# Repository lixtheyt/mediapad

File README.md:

<div align="center">

# MediaPad

**A 9 key hackpad with a rotary encoder, an OLED display and 20 LEDs that controls whatever is playing on your computer, and shows it to you on its own screen.**

<!-- HELYX_STATUS_START -->
<!-- HELYX_STATUS_END -->

</div>

## Table of contents

- [Features](#features)
- [Video](#video)
- [Quick start](#quick-start)
- [Build it yourself](#build-it-yourself)
    - [BOM](#bom)
    - [Case](#case)
    - [PCB](#pcb)
    - [IRL results](#irl-results)
- [Firmware](#firmware)
    - [Two builds](#two-builds)
    - [The keys](#the-keys)
    - [Rotary encoder](#rotary-encoder)
    - [RGB](#rgb)
    - [Help browser](#help-browser)
    - [OLED](#oled)
    - [Hidden key combos](#hidden-key-combos)
- [Companion app](#companion-app)
- [Credits](#credits)
- [License](#license)

## Features

- **128x32 OLED display**, with the title, artist and progress of whatever is playing.
- **EC11 rotary encoder**, which does something different in each of its six modes.
- **20 SK6812 MINI-E LEDs**. We gotta make somethin' for party nah??
- **Eight media keys**, the same on every mode except RGB, where they mix the colours.
- **A cool designed case**, printed in 8 pieces.

## Video

Click the picture to watch it.

## Quick start

Everything you need to make one is in [`Production`](Production):

| File | What it is |
| --- | --- |
| `gerbers.zip` | the PCB, ready to send to a manufacturer |
| `topCase.stl`, `middleCase.stl`, `bottomCase.stl` | the three parts of the case |
| `spacer.stl` | the spacer for the glow, print 6 |
| `support_display.stl` | the support for the OLED display |
| `mediapad_rev20_lixtheyt.uf2` | firmware for a board with all 20 LEDs |
| `mediapad_rev16_lixtheyt.uf2` | firmware for a board with 16 LEDs |

To flash it, hold the top left key while plugging the board in. It shows up as a drive on your
computer. Copy the `.uf2` that matches your board onto it and it restarts by itself.

Then start [`Companion/mediapad_tray.exe`](Companion), so the display knows what is playing.

## Build it yourself

### BOM

- 8x Cherry MX Switches
- 8x Keycaps
- 6x M3x5x4 Heatset inserts
- 6x M3x16mm Screws
- 8x 1N4148 DO-35 Diodes
- 16x/20x SK6812 MINI-E LEDs (16x = encoder has no LEDs)
- 1x 0.91" 128x32 OLED Display
- 1x EC11 Rotary Encoder
- 1x XIAO RP2040
- 1x Case (1x bottom case, 1x middle case, 1x top case)
- 6x Spacers (printed part)
- 1x Display Support (printed part, use a double-sided tape so it will hold)

### Case

Everything fits together using 6 M3 Bolts and heatset inserts. 4 for the case and 2 for the PCB.

It has 8 separate printed pieces.
3 are parts of the case, 1 is a spacer for the glow and 1 is for the OLED display as a support.

### PCB

I made my PCB inside KiCad.
Libraries I used were originally from the Hackpad website but I also used some that I had found on [grabcad](https://grabcad.com/library).

**Schematic**

**Board**

### IRL results

<div align="center">

</div>

## Firmware

This hackpad uses [QMK](https://qmk.fm/) firmware for everything.

### Two builds

The board exists in two LED populations, so the firmware ships as two revisions.
They differ only in the LED map keys, encoder and OLED are shared.

| Revision | LEDs | Board |
| --- | --- | --- |
| `rev20` | D1-D20 | fully populated |
| `rev16` | D1-D16 | built without the four LEDs ringing the encoder |

The four LEDs `rev16` leaves out are last in the WS2812 chain, so the remaining
sixteen still light normally. The idle screen prints the count
(`mediapad 16 LED`) so you can tell which build is on the board.

```bash
make mediapad/rev20:lixtheyt
```

### The keys

All eight switches are media keys, on every mode except RGB. Only what the
encoder does changes from mode to mode.

```
SW1 play/pause   SW2 rewind       SW3 fast forward   SW6 mute
SW4 prev track   SW5 next track
SW7 repeat       SW8 shuffle      SW9 = the encoder
```

### Rotary encoder

Clicking the encoder opens a mode picker that **previews** rather than switches:

* **Click** - opens it, showing the mode you are already in
* **Turn** - walks the list, nothing has changed yet
* **Click again** - confirms, and only now does the mode change
* **Wait** - it lapses and you stay exactly where you were

1. **Volume** - volume up / down
2. **Track skip** - next / previous track
3. **Arrows** - arrow up / down
4. **Scroll** - mouse wheel up / down
5. **Zoom** - zoom in / out, sent as Ctrl + wheel so it does not depend on your
   keyboard layout
6. **RGB** - the lighting, below

### RGB

RGB contains 16 effects. The first six run their own colours
(Pinwheel, Vortex, Rainbow wave, Chevron, Splash, Raindrops), the other ten come
out in whatever you mix, and several of those react to keypresses and spread
outward from the key you hit.

The keys aim the dial, and the dial does the changing:

```
SW1 red   SW2 green   SW3 blue   SW6 brightness   SW4 effect list
```

Whatever you set is remembered. The colour, the brightness and the effect are saved a few seconds
after you stop turning the dial, so they are still there after you unplug the board.

### Help browser

Press **play/pause + rewind together** if you forget what a key does. Turn the
encoder to walk the list, click it for the answer, press anything to back out.
The list follows whichever mode you opened it from.

The LEDs either side of that key light up
with the key itself as the dark gap between them, and the display spells the
position out in words. The words are the part that always works. The LED grid
sits about half a key pitch off the switch grid, so no single LED can point at a
key without also looking like it points at its neighbour.

### OLED

While something is playing, a scrolling title and artist, a progress bar, and a
bottom row carrying play/pause on the left, the clock, and shuffle / repeat
symbols on the right. The clock runs locally rather than echoing the host,
because Windows only refreshes its playback position every few seconds.

Otherwise: the board name and LED count, the current mode, and either
`waiting for app` (nothing arriving) or `nothing playing` (the app is connected,
but Windows has no media session).

The display turns itself off after five minutes with no key pressed, no turn of the encoder and
nothing playing, so the idle screen does not burn into the OLED. Any key, any turn or a track that
starts playing turns it back on.

### Hidden key combos

Armed on the media modes only. On the RGB mode those same switches are colour
controls.

| Hold | For | Does |
| --- | --- | --- |
| rewind + fast forward + mute | 5 s | bootloader |
| repeat + shuffle + mute | 5 s | clear EEPROM |
| rewind + fast forward | 2 s | reboot |
| repeat + shuffle | 2 s | toggle debug |

You can also reach the bootloader by holding the top left key while plugging in,
or by double-tapping the reset button on the XIAO.

## Companion app

`Companion/mediapad_tray.exe` is a portable application made in Python that feeds MediaPad with the latest
information about current played media on your computer. Without it the OLED shows the board name and
`waiting for app`, everything except the now-playing screen still works.

As I have mentioned... it is a portable application. That means you don't have to install anything.
Just open, mess with it in the tray (where background applications are located) and make sure to enable
the setting that allows it to open on start up of your computer, so you don't have to turn it on manually
every time you turn on your computer. If you've got no idea where the tray with the background applications
is located then please, [google it](https://www.google.com/search?q=Where+is+the+background+tray+located?).

## Credits

- [QMK](https://qmk.fm/), the firmware everything here runs on.
- [KiCad](https://www.kicad.org/) for the PCB and [Blender](https://www.blender.org/) for the case.
- The [Hackpad](https://hackpad.hackclub.com/) guide by Hack Club, where the first libraries came from.

I want to note out that the firmware was mostly done by AI due to my limited C knowledge
and the difficulty to create a firmware that does such advanced things.

## License

[MIT](LICENSE)

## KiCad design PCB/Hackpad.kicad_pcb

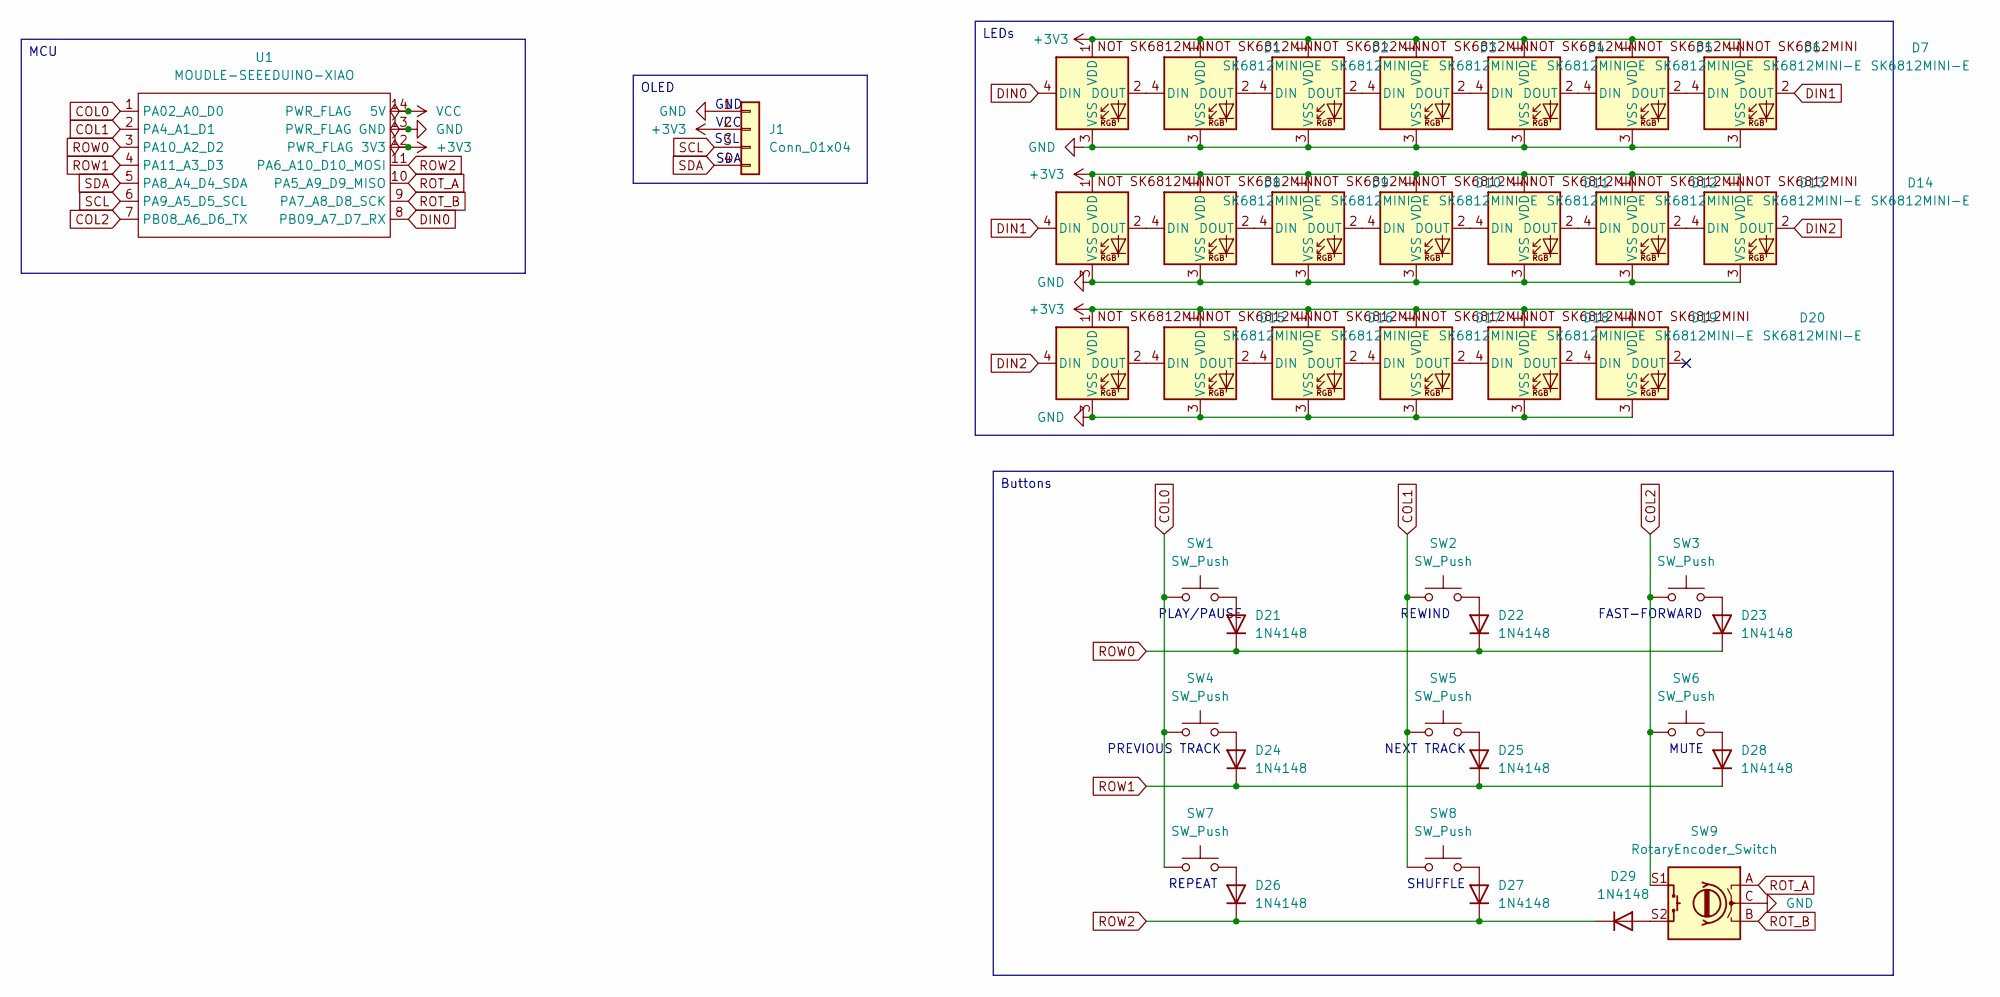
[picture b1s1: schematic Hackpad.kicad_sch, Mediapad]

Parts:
D1, D2, D3, D4, D5, D6, D7, D8, D9, D10, D11, D12, D13, D14, D15, D16, D17, D18, D19, D20: SK6812MINI-E; SK6812MINI-E_fixed
D21, D22, D23, D24, D25, D26, D27, D28, D29: 1N4148; D_DO-35_SOD27_P7.62mm_Horizontal
J1: Conn_01x04; SSD1306-0.91-OLED-4pin-128x32
SW1, SW2, SW3, SW4, SW5, SW6, SW7, SW8: SW_Push; SW_Cherry_MX_1.00u_PCB
SW9: RotaryEncoder_Switch; RotaryEncoder_Alps_EC11E-Switch_Vertical_H20mm
U1: MOUDLE-SEEEDUINO-XIAO; XIAO-Generic-Hybrid-14P-2.54-21X17.8MM

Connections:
+3V3: D1.1 (VDD), D2.1 (VDD), D3.1 (VDD), D4.1 (VDD), D5.1 (VDD), D6.1 (VDD), D7.1 (VDD), D8.1 (VDD), D9.1 (VDD), D10.1 (VDD), D11.1 (VDD), D12.1 (VDD), D13.1 (VDD), D14.1 (VDD), D15.1 (VDD), D16.1 (VDD), D17.1 (VDD), D18.1 (VDD), D19.1 (VDD), D20.1 (VDD), J1.2, U1.12 (3V3)
COL0: SW1.1, SW4.1, SW7.1, U1.1 (PA02_A0_D0)
COL1: SW2.1, SW5.1, SW8.1, U1.2 (PA4_A1_D1)
COL2: SW3.1, SW6.1, SW9.S1, U1.7 (PB08_A6_D6_TX)
DIN0: D1.4 (DIN), U1.8 (PB09_A7_D7_RX)
DIN1: D7.2 (DOUT), D8.4 (DIN)
DIN2: D14.2 (DOUT), D15.4 (DIN)
GND: D1.3 (VSS), D2.3 (VSS), D3.3 (VSS), D4.3 (VSS), D5.3 (VSS), D6.3 (VSS), D7.3 (VSS), D8.3 (VSS), D9.3 (VSS), D10.3 (VSS), D11.3 (VSS), D12.3 (VSS), D13.3 (VSS), D14.3 (VSS), D15.3 (VSS), D16.3 (VSS), D17.3 (VSS), D18.3 (VSS), D19.3 (VSS), D20.3 (VSS), J1.1, SW9.C, U1.13 (GND)
unnamed: D1.2 (DOUT), D2.4 (DIN)
unnamed: D2.2 (DOUT), D3.4 (DIN)
unnamed: D3.2 (DOUT), D4.4 (DIN)
unnamed: D4.2 (DOUT), D5.4 (DIN)
unnamed: D5.2 (DOUT), D6.4 (DIN)
unnamed: D6.2 (DOUT), D7.4 (DIN)
unnamed: D8.2 (DOUT), D9.4 (DIN)
unnamed: D9.2 (DOUT), D10.4 (DIN)
unnamed: D10.2 (DOUT), D11.4 (DIN)
unnamed: D11.2 (DOUT), D12.4 (DIN)
unnamed: D12.2 (DOUT), D13.4 (DIN)
unnamed: D13.2 (DOUT), D14.4 (DIN)
unnamed: D15.2 (DOUT), D16.4 (DIN)
unnamed: D16.2 (DOUT), D17.4 (DIN)
unnamed: D17.2 (DOUT), D18.4 (DIN)
unnamed: D18.2 (DOUT), D19.4 (DIN)
unnamed: D19.2 (DOUT), D20.4 (DIN)
unnamed: D21.2 (A), SW1.2
unnamed: D22.2 (A), SW2.2
unnamed: D23.2 (A), SW3.2
unnamed: D24.2 (A), SW4.2
unnamed: D25.2 (A), SW5.2
unnamed: D26.2 (A), SW7.2
unnamed: D27.2 (A), SW8.2
unnamed: D28.2 (A), SW6.2
unnamed: D29.2 (A), SW9.S2
ROT_A: SW9.A, U1.10 (PA5_A9_D9_MISO)
ROT_B: SW9.B, U1.9 (PA7_A8_D8_SCK)
ROW0: D21.1 (K), D22.1 (K), D23.1 (K), U1.3 (PA10_A2_D2)
ROW1: D24.1 (K), D25.1 (K), D28.1 (K), U1.4 (PA11_A3_D3)
ROW2: D26.1 (K), D27.1 (K), D29.1 (K), U1.11 (PA6_A10_D10_MOSI)
SCL: J1.3, U1.6 (PA9_A5_D5_SCL)
SDA: J1.4, U1.5 (PA8_A4_D4_SDA)
VCC: U1.14 (5V)

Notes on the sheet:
SDA
REWIND
PREVIOUS TRACK
REPEAT
VCC
SHUFFLE
GND
PLAY/PAUSE
SCL
MUTE
FAST-FORWARD
NEXT TRACK
OLED
LEDs
Buttons
MCU

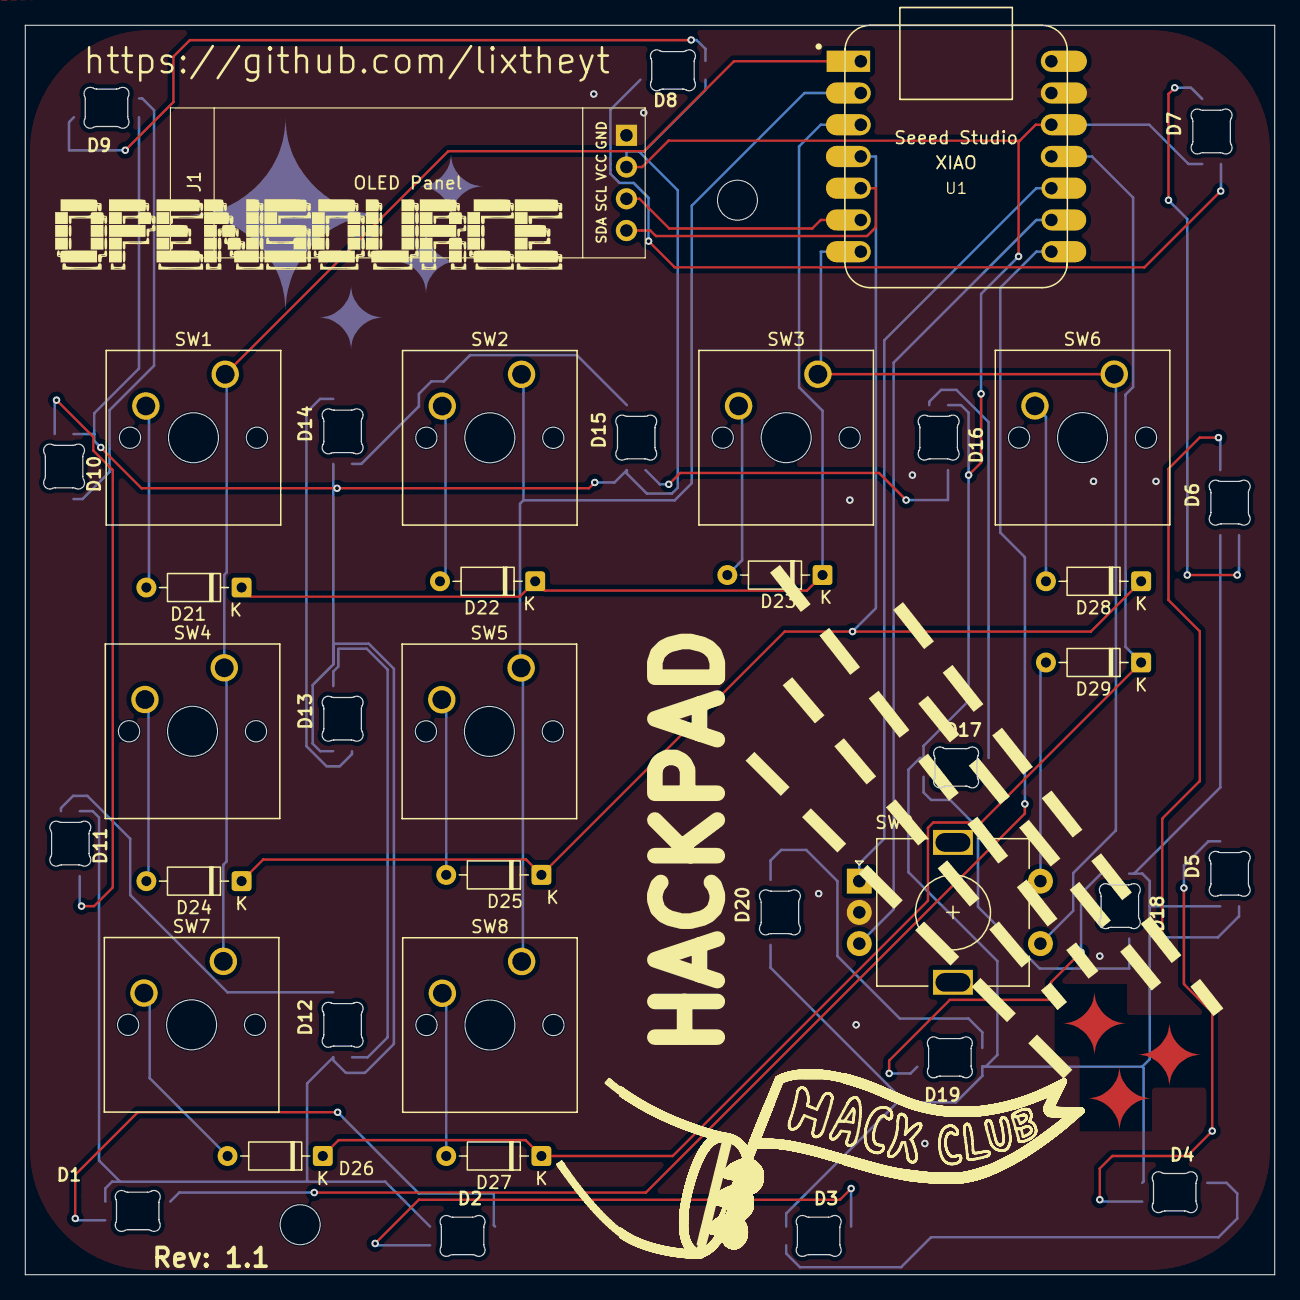
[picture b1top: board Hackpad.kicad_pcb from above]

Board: 2 copper layers, 100.0 x 100.0 mm, 42 parts (0 on the bottom side), 41 nets.

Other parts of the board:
REF98, REF99: MountingHole_3.2mm_M3

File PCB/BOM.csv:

"Reference","Qty","Value","DNP","Exclude from BOM","Exclude from Board","Footprint","Datasheet"
"D1,D2,D3,D4,D5,D6,D7,D8,D9,D10,D11,D12,D13,D14,D15,D16,D17,D18,D19,D20","20","SK6812MINI-E","","","","footprints:SK6812MINI-E_fixed","https://www.lcsc.com/datasheet/C5149201.pdf"
"D21,D22,D23,D24,D25,D26,D27,D28,D29","9","1N4148","","","","Diode_THT:D_DO-35_SOD27_P7.62mm_Horizontal","https://assets.nexperia.com/documents/data-sheet/1N4148_1N4448.pdf"
"J1","1","Conn_01x04","","","","oled:SSD1306-0.91-OLED-4pin-128x32",""
"SW1,SW2,SW3,SW4,SW5,SW6,SW7,SW8","8","SW_Push","","","","Button_Switch_Keyboard:SW_Cherry_MX_1.00u_PCB",""
"SW9","1","RotaryEncoder_Switch","","","","Rotary_Encoder:RotaryEncoder_Alps_EC11E-Switch_Vertical_H20mm",""
"U1","1","MOUDLE-SEEEDUINO-XIAO","","","","footprints:XIAO-Generic-Hybrid-14P-2.54-21X17.8MM",""
